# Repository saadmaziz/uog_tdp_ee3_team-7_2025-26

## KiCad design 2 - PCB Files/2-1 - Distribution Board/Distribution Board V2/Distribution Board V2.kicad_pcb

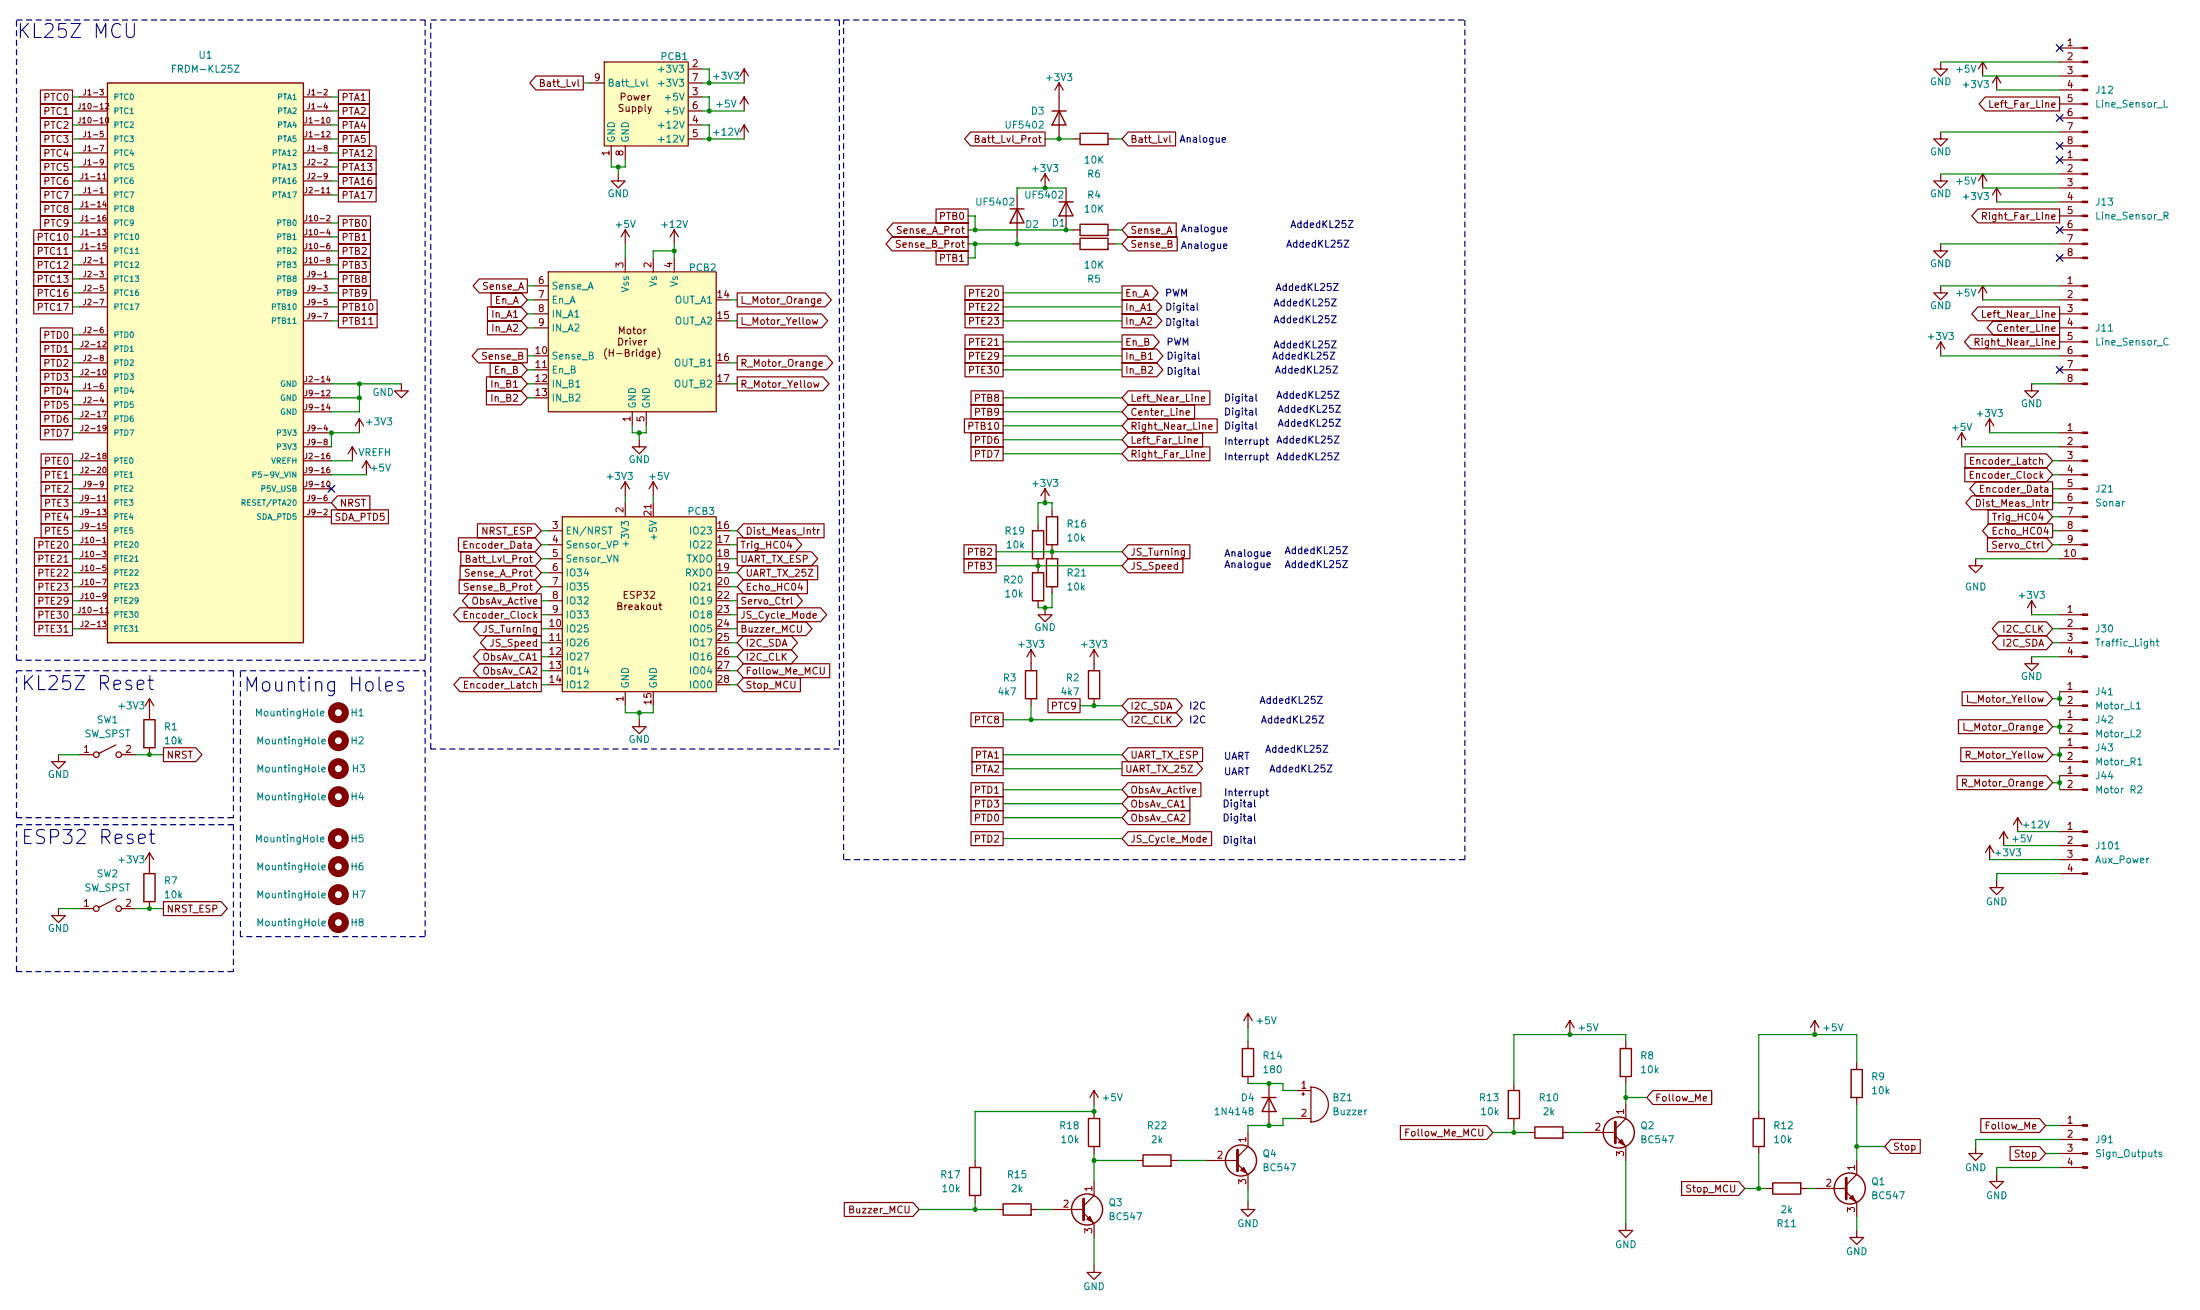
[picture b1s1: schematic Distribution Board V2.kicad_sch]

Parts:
BZ1: Buzzer; Buzzer_D14mm_H7mm_P10mm
D1, D2, D3: UF5402; D_DO-201AD_P15.24mm_Horizontal
D4: 1N4148; D_DO-35_SOD27_P7.62mm_Horizontal
H1, H2, H3, H4, H5, H6, H7, H8: MountingHole; MountingHole_3.2mm_M3
J11: Line_Sensor_C; Molex_KK-254_AE-6410-08A_1x08_P2.54mm_Vertical
J12: Line_Sensor_L; Molex_KK-254_AE-6410-08A_1x08_P2.54mm_Vertical
J13: Line_Sensor_R; Molex_KK-254_AE-6410-08A_1x08_P2.54mm_Vertical
J21: Sonar; Molex_KK-254_AE-6410-10A_1x10_P2.54mm_Vertical
J30: Traffic_Light; Molex_KK-254_AE-6410-04A_1x04_P2.54mm_Vertical
J41: Motor_L1; Molex_KK-254_AE-6410-02A_1x02_P2.54mm_Vertical
J42: Motor_L2; Molex_KK-254_AE-6410-02A_1x02_P2.54mm_Vertical
J43: Motor_R1; Molex_KK-254_AE-6410-02A_1x02_P2.54mm_Vertical
J44: Motor R2; Molex_KK-254_AE-6410-02A_1x02_P2.54mm_Vertical
J91: Sign_Outputs; Molex_KK-254_AE-6410-04A_1x04_P2.54mm_Vertical
J101: Aux_Power; Molex_KK-254_AE-6410-04A_1x04_P2.54mm_Vertical
PCB1: PSU; Power_Supply
PCB2: Motor_Driver; Motor_Controller
PCB3: ESP32; ESP32_Breakout
Q1, Q2, Q3, Q4: BC547; TO-92_Inline_Wide
R1, R7, R8, R9, R12, R13, R16, R17, R18, R19, R20, R21: 10k; R_0805_2012Metric_Pad1.20x1.40mm_HandSolder
R2, R3: 4k7; R_0805_2012Metric_Pad1.20x1.40mm_HandSolder
R4, R5, R6: 10K; R_0805_2012Metric_Pad1.20x1.40mm_HandSolder
R10, R11, R15, R22: 2k; R_0805_2012Metric_Pad1.20x1.40mm_HandSolder
R14: 180; R_0805_2012Metric_Pad1.20x1.40mm_HandSolder
SW1, SW2: SW_SPST; SW_PUSH_1P1T_6x3.5mm_H4.3_APEM_MJTP1243
U1: FRDM-KL25Z

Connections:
+3V3: D1.1 (K), D2.1 (K), D3.1 (K), J11.6, J12.4, J13.4, J21.1, J30.1, J101.3, PCB1.2 (+3V3), PCB1.7 (+3V3), PCB3.2 (+3V3), R1.1, R2.1, R3.1, R7.1, R16.2, R19.2, U1.J9-4 (P3V3), U1.J9-8 (P3V3)
+5V: J11.2, J12.3, J13.3, J21.2, J101.2, PCB1.3 (+5V), PCB1.6 (+5V), PCB2.3 (Vss), PCB3.21 (+5V), R8.1, R9.1, R12.1, R13.1, R14.1, R17.1, R18.1, U1.J9-16 (P5-9V_VIN)
+12V: J101.1, PCB1.4 (+12V), PCB1.5 (+12V), PCB2.2 (Vs), PCB2.4 (Vs)
Batt_Lvl: PCB1.9 (Batt_Lvl), R6.2
Batt_Lvl_Prot: D3.2 (A), PCB3.5 (Sensor_VN), R6.1
Buzzer_MCU: PCB3.24 (IO05), R15.1, R17.2
Center_Line: J11.4, U1.J9-3 (PTB9)
Dist_Meas_Intr: J21.6, PCB3.16 (IO23)
Echo_HC04: J21.8, PCB3.20 (IO21)
En_A: PCB2.7 (En_A), U1.J10-1 (PTE20)
En_B: PCB2.11 (En_B), U1.J10-3 (PTE21)
Encoder_Clock: J21.4, PCB3.9 (IO33)
Encoder_Data: J21.5, PCB3.4 (Sensor_VP)
Encoder_Latch: J21.3, PCB3.14 (IO12)
Follow_Me: J91.1, Q2.1 (C), R8.2
Follow_Me_MCU: PCB3.27 (IO04), R10.1, R13.2
GND: J11.1, J11.8, J12.2, J12.7, J13.2, J13.7, J21.10, J30.4, J91.2, J91.4, J101.4, PCB1.1 (GND), PCB1.8 (GND), PCB2.1 (GND), PCB2.5 (GND), PCB3.1 (GND), PCB3.15 (GND), Q1.3 (E), Q2.3 (E), Q3.3 (E), Q4.3 (E), R20.1, R21.1, SW1.1 (A), SW2.1 (A), U1.J2-14 (GND), U1.J9-12 (GND), U1.J9-14 (GND)
I2C_CLK: J30.2, PCB3.26 (IO16), R3.2, U1.J1-14 (PTC8)
I2C_SDA: J30.3, PCB3.25 (IO17), R2.2, U1.J1-16 (PTC9)
In_A1: PCB2.8 (IN_A1), U1.J10-5 (PTE22)
In_A2: PCB2.9 (IN_A2), U1.J10-7 (PTE23)
In_B1: PCB2.12 (IN_B1), U1.J10-9 (PTE29)
In_B2: PCB2.13 (IN_B2), U1.J10-11 (PTE30)
JS_Cycle_Mode: PCB3.23 (IO18), U1.J2-8 (PTD2)
JS_Speed: PCB3.11 (IO26), R19.1, R20.2, U1.J10-8 (PTB3)
JS_Turning: PCB3.10 (IO25), R16.1, R21.2, U1.J10-6 (PTB2)
L_Motor_Orange: J42.1, J42.2, PCB2.14 (OUT_A1)
L_Motor_Yellow: J41.1, J41.2, PCB2.15 (OUT_A2)
Left_Far_Line: J12.5, U1.J2-17 (PTD6)
Left_Near_Line: J11.3, U1.J9-1 (PTB8)
NRST: R1.2, SW1.2 (B), U1.J9-6 (RESET/PTA20)
NRST_ESP: PCB3.3 (EN/NRST), R7.2, SW2.2 (B)
unnamed: BZ1.1 (+), D4.1 (K), R14.2
unnamed: BZ1.2 (-), D4.2 (A), Q4.1 (C)
unnamed: Q1.2 (B), R11.2
unnamed: Q2.2 (B), R10.2
unnamed: Q3.2 (B), R15.2
unnamed: Q3.1 (C), R18.2, R22.1
unnamed: Q4.2 (B), R22.2
ObsAv_Active: PCB3.8 (IO32), U1.J2-12 (PTD1)
ObsAv_CA1: PCB3.12 (IO27), U1.J2-10 (PTD3)
ObsAv_CA2: PCB3.13 (IO14), U1.J2-6 (PTD0)
PTA1: PCB3.18 (TXDO), U1.J1-2 (PTA1)
PTA2: PCB3.19 (RXDO), U1.J1-4 (PTA2)
PTA4: U1.J1-10 (PTA4)
PTA5: U1.J1-12 (PTA5)
PTA12: U1.J1-8 (PTA12)
PTA13: U1.J2-2 (PTA13)
PTA16: U1.J2-9 (PTA16)
PTA17: U1.J2-11 (PTA17)
PTB0: D1.2 (A), PCB3.6 (IO34), R4.1, U1.J10-2 (PTB0)
PTB1: D2.2 (A), PCB3.7 (IO35), R5.1, U1.J10-4 (PTB1)
PTB10: J11.5, U1.J9-5 (PTB10)
PTB11: U1.J9-7 (PTB11)
PTC0: U1.J1-3 (PTC0)
PTC1: U1.J10-12 (PTC1)
PTC2: U1.J10-10 (PTC2)
PTC3: U1.J1-5 (PTC3)
PTC4: U1.J1-7 (PTC4)
PTC5: U1.J1-9 (PTC5)
PTC6: U1.J1-11 (PTC6)
PTC7: U1.J1-1 (PTC7)
PTC10: U1.J1-13 (PTC10)
PTC11: U1.J1-15 (PTC11)
PTC12: U1.J2-1 (PTC12)
PTC13: U1.J2-3 (PTC13)
PTC16: U1.J2-5 (PTC16)
PTC17: U1.J2-7 (PTC17)
PTD4: U1.J1-6 (PTD4)
PTD5: U1.J2-4 (PTD5)
PTD7: J13.5, U1.J2-19 (PTD7)
PTE0: U1.J2-18 (PTE0)
PTE1: U1.J2-20 (PTE1)
PTE2: U1.J9-9 (PTE2)
PTE3: U1.J9-11 (PTE3)
PTE4: U1.J9-13 (PTE4)
PTE5: U1.J9-15 (PTE5)
PTE31: U1.J2-13 (PTE31)
R_Motor_Orange: J44.1, J44.2, PCB2.16 (OUT_B1)
R_Motor_Yellow: J43.1, J43.2, PCB2.17 (OUT_B2)
SDA_PTD5: U1.J9-2 (SDA_PTD5)
Sense_A: PCB2.6 (Sense_A), R4.2
Sense_B: PCB2.10 (Sense_B), R5.2
Servo_Ctrl: J21.9, PCB3.22 (IO19)
Stop: J91.3, Q1.1 (C), R9.2
Stop_MCU: PCB3.28 (IO00), R11.1, R12.2
Trig_HC04: J21.7, PCB3.17 (IO22)
VREFH: U1.J2-16 (VREFH)

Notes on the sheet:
Analogue
UART
Mounting Holes
Interrupt
PWM
AddedKL25Z
Digital
ESP32 Reset
KL25Z Reset
KL25Z MCU
I2C

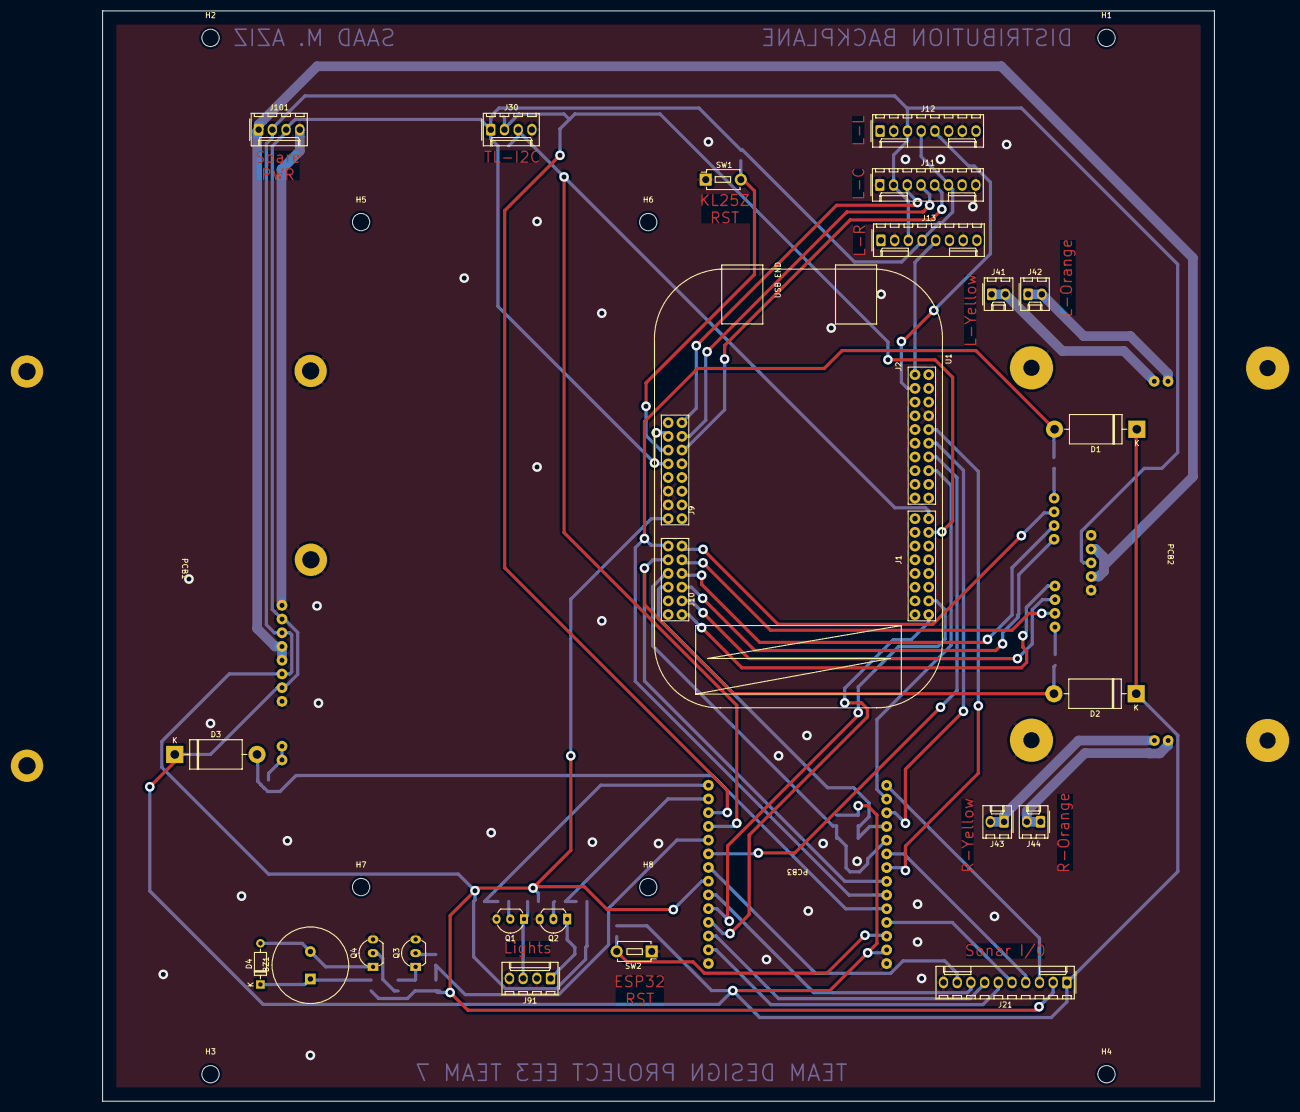
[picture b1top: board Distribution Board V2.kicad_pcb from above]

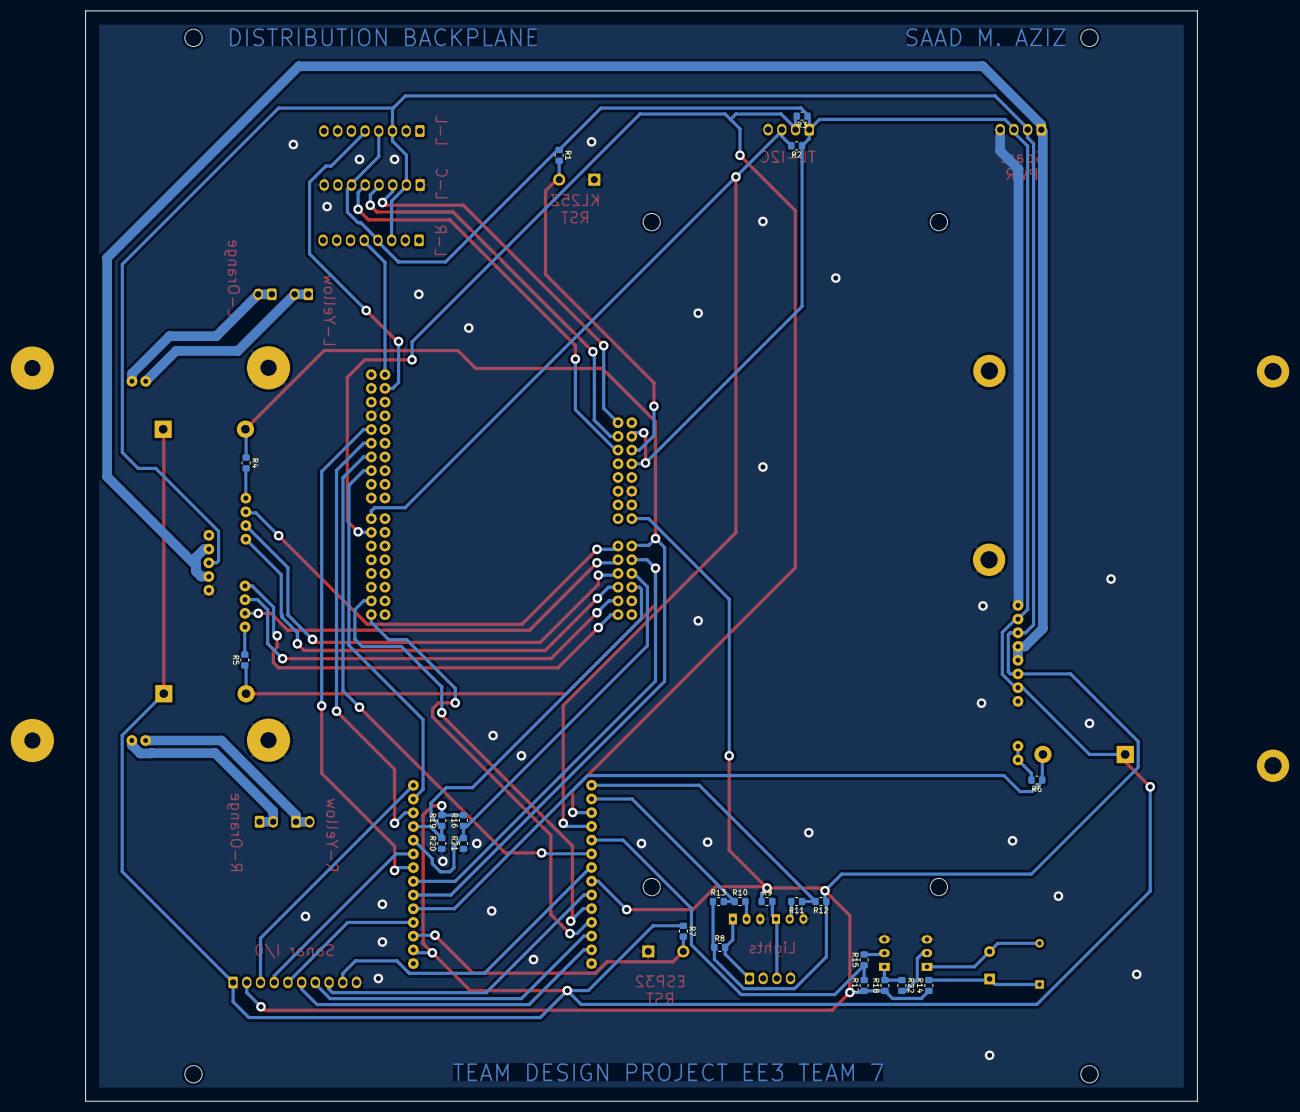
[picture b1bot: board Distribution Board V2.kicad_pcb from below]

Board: 2 copper layers, 206.0 x 202.0 mm, 56 parts (22 on the bottom side), 56 nets.

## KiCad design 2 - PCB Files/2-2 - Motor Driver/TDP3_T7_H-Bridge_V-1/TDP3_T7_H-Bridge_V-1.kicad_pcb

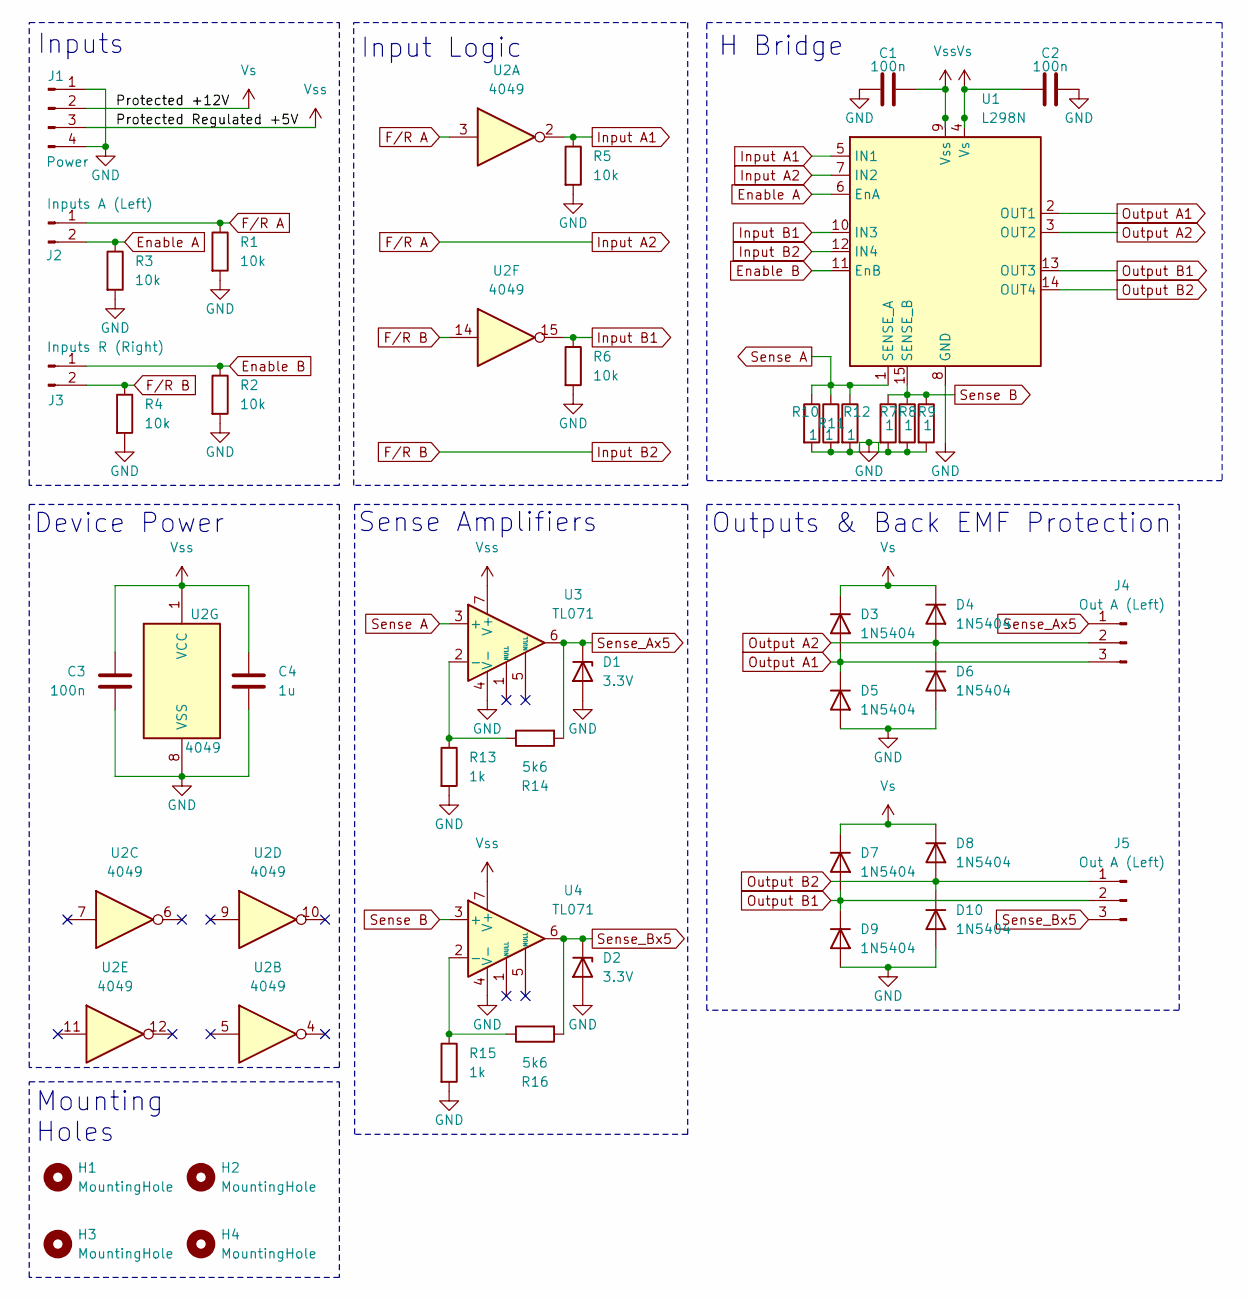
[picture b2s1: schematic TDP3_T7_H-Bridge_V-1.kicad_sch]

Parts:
C1, C2, C3: 100n; C_0805_2012Metric_Pad1.18x1.45mm_HandSolder
C4: 1u; C_0805_2012Metric_Pad1.18x1.45mm_HandSolder
D1, D2: 3.3V; D_DO-41_SOD81_P7.62mm_Horizontal
D3, D4, D5, D6, D7, D8, D9, D10: 1N5404; D_DO-201AD_P12.70mm_Horizontal
H1, H2, H3, H4: MountingHole; MountingHole_3.2mm_M3
J1: Power; Molex_KK-254_AE-6410-04A_1x04_P2.54mm_Vertical
J2: Inputs A (Left); Molex_KK-254_AE-6410-02A_1x02_P2.54mm_Vertical
J3: Inputs R (Right); Molex_KK-254_AE-6410-02A_1x02_P2.54mm_Vertical
J4, J5: Out A (Left); Molex_KK-254_AE-6410-03A_1x03_P2.54mm_Vertical
R1, R2, R3, R4, R5, R6: 10k; R_0805_2012Metric_Pad1.20x1.40mm_HandSolder
R7, R8, R9, R10, R11, R12: 1; R_Axial_DIN0207_L6.3mm_D2.5mm_P2.54mm_Vertical
R13, R15: 1k; R_0805_2012Metric_Pad1.20x1.40mm_HandSolder
R14, R16: 5k6; R_0805_2012Metric_Pad1.20x1.40mm_HandSolder
U1: L298N; L298N Heatsink
U2: 4049; DIP-16_W7.62mm
U3, U4: TL071; DIP-8_W7.62mm

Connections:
Enable A: J2.2, R3.1, U1.6 (EnA)
Enable B: J3.1, R2.1, U1.11 (EnB)
F/R A: J2.1, R1.1, U1.7 (IN2), U2.3
F/R B: J3.2, R4.1, U1.12 (IN4), U2.14
GND: C1.1, C2.2, C3.2, C4.2, D1.2 (A), D2.2 (A), D5.2 (A), D6.2 (A), D9.2 (A), D10.2 (A), J1.1, J1.4, R1.2, R2.2, R3.2, R4.2, R5.2, R6.2, R7.2, R8.2, R9.2, R10.2, R11.2, R12.2, R13.2, R15.2, U1.8 (GND), U2.8 (VSS), U3.4 (V-), U4.4 (V-)
Input A1: R5.1, U1.5 (IN1), U2.2
Input B1: R6.1, U1.10 (IN3), U2.15
unnamed: R13.1, R14.1, U3.2 (-)
unnamed: R15.1, R16.1, U4.2 (-)
Output A1: D3.2 (A), D5.1 (K), J4.3, U1.2 (OUT1)
Output A2: D4.2 (A), D6.1 (K), J4.2, U1.3 (OUT2)
Output B1: D7.2 (A), D9.1 (K), J5.2, U1.13 (OUT3)
Output B2: D8.2 (A), D10.1 (K), J5.1, U1.14 (OUT4)
Sense A: R10.1, R11.1, R12.1, U1.1 (SENSE_A), U3.3 (+)
Sense B: R7.1, R8.1, R9.1, U1.15 (SENSE_B), U4.3 (+)
Sense_Ax5: D1.1 (K), J4.1, R14.2, U3.6
Sense_Bx5: D2.1 (K), J5.3, R16.2, U4.6
Vs: C2.1, D3.1 (K), D4.1 (K), D7.1 (K), D8.1 (K), J1.2, U1.4 (Vs)
Vss: C1.2, C3.1, C4.1, J1.3, U1.9 (Vss), U2.1 (VCC), U3.7 (V+), U4.7 (V+)

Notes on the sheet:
Device Power
Input Logic
Mounting Holes
Inputs
Outputs & Back EMF Protection
H Bridge
Sense Amplifiers

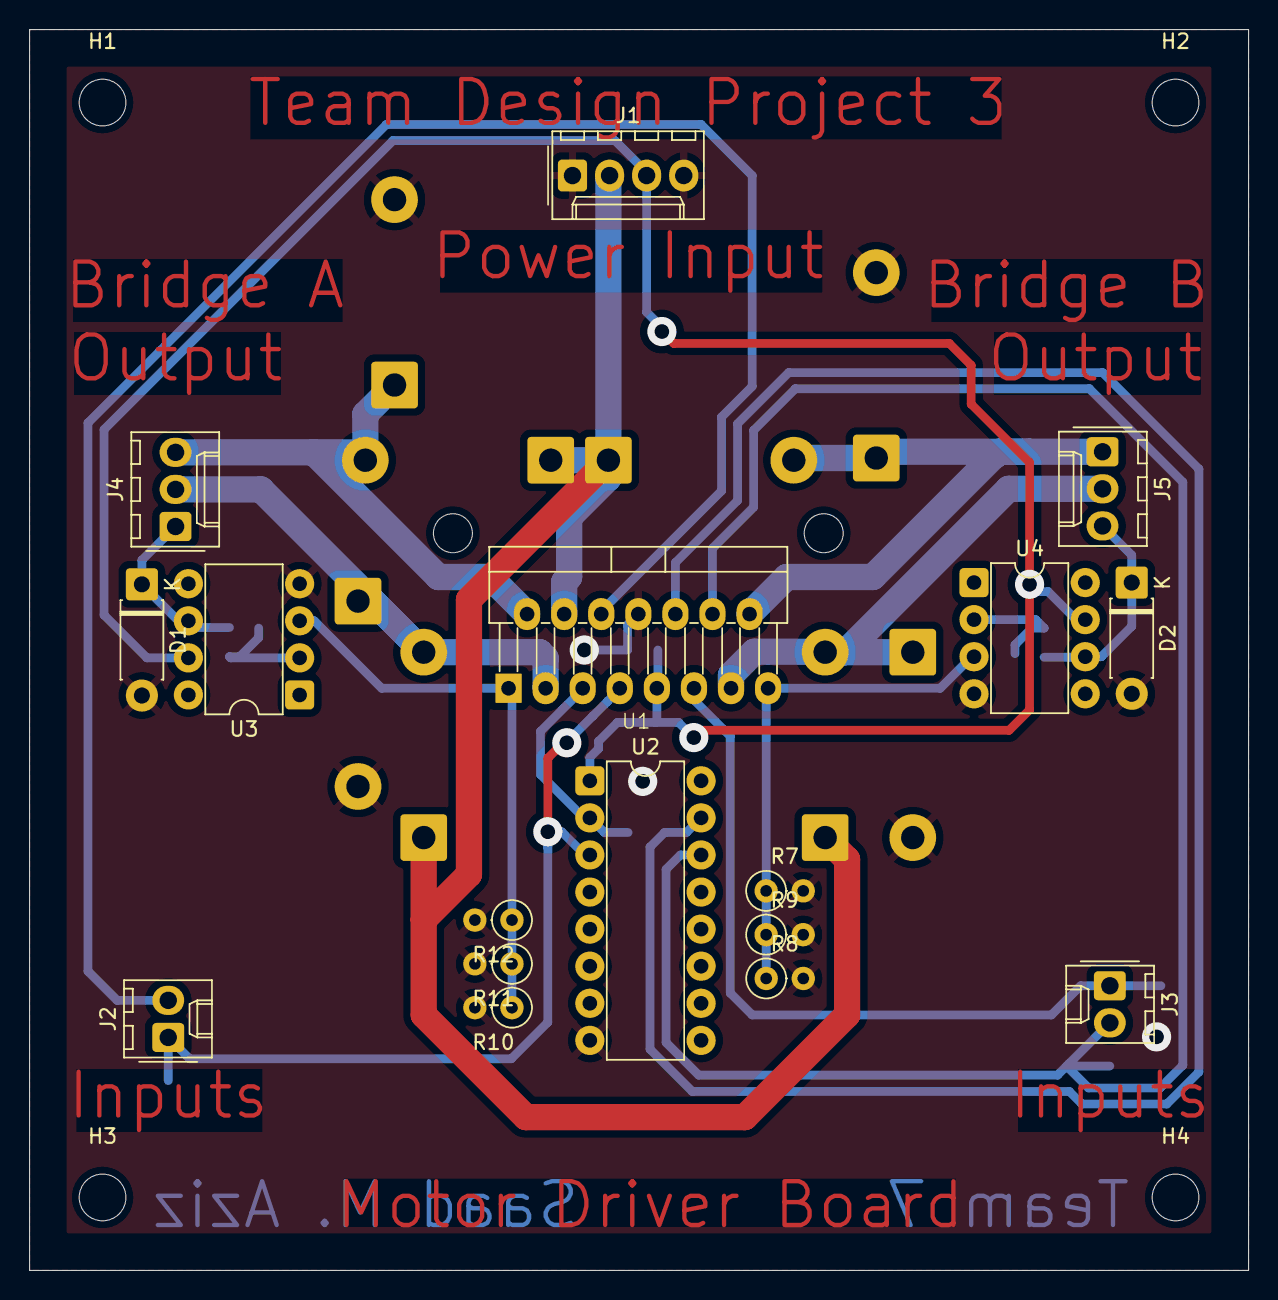
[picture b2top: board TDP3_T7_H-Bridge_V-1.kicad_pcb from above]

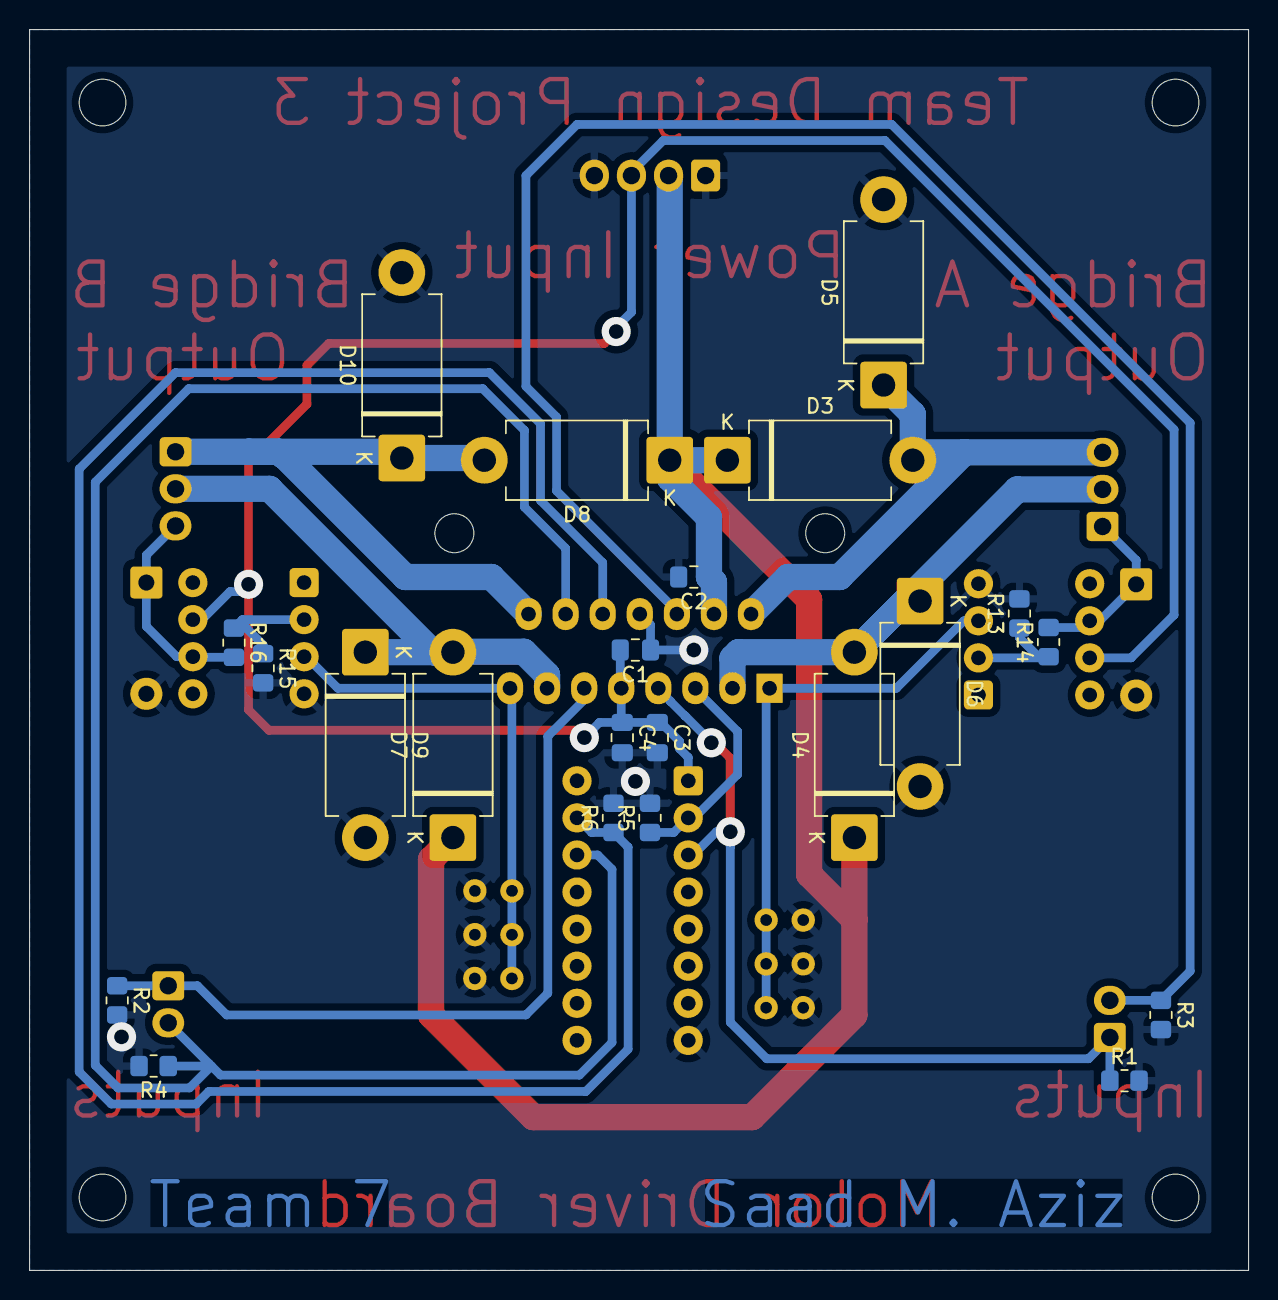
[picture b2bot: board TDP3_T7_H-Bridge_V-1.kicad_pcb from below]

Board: 2 copper layers, 83.5 x 85.0 mm, 43 parts (22 on the bottom side), 19 nets.

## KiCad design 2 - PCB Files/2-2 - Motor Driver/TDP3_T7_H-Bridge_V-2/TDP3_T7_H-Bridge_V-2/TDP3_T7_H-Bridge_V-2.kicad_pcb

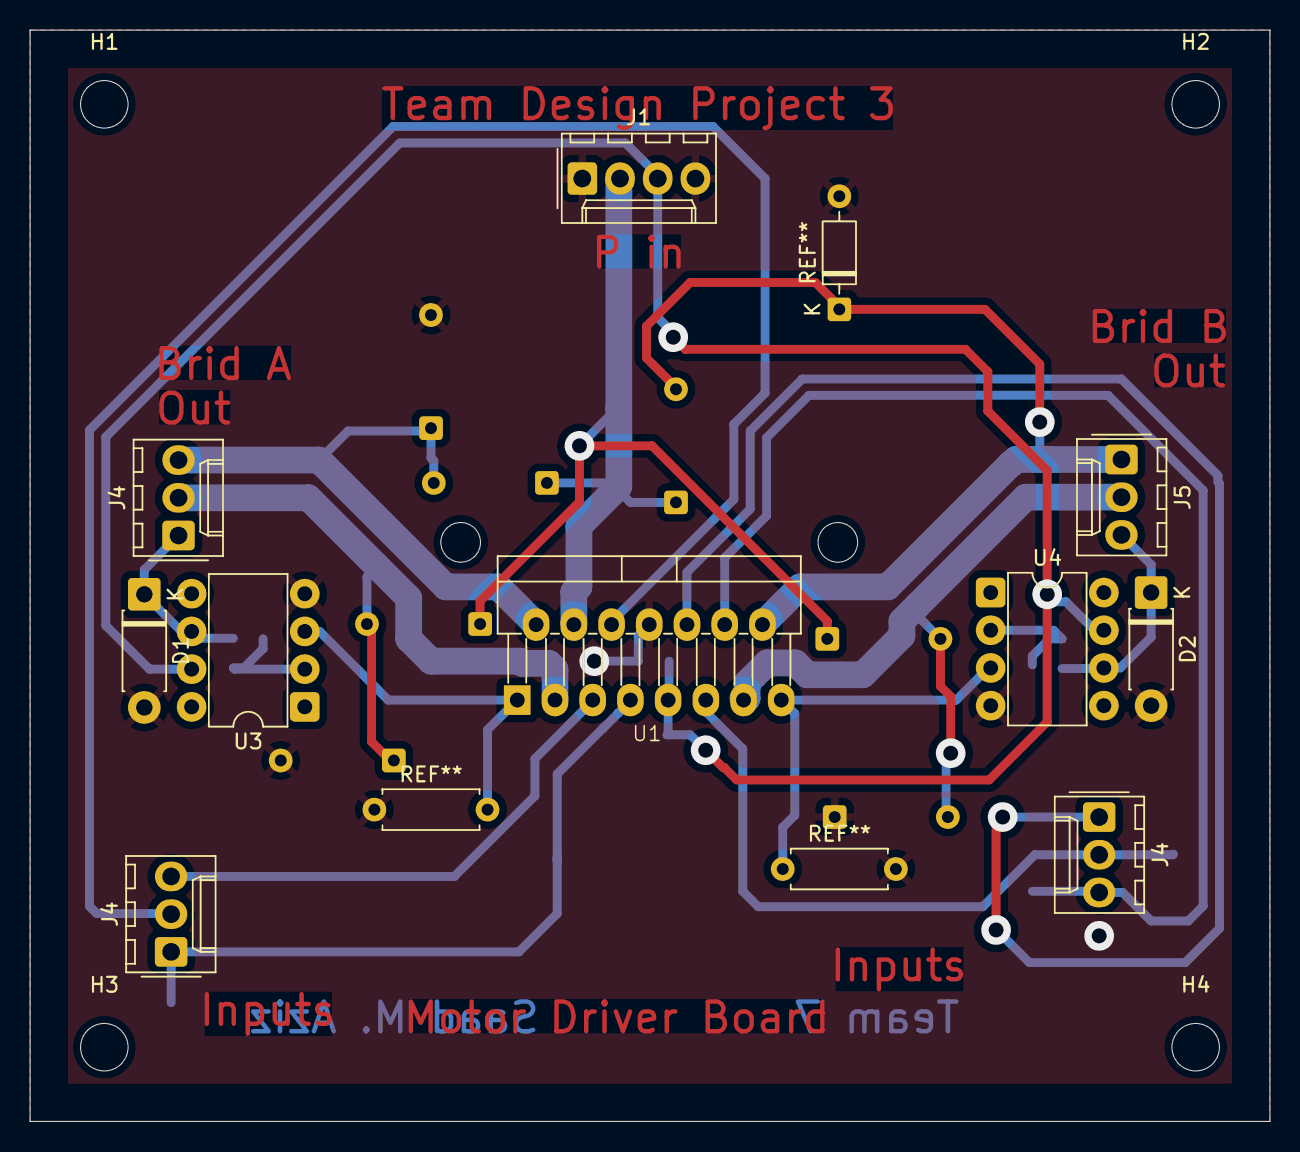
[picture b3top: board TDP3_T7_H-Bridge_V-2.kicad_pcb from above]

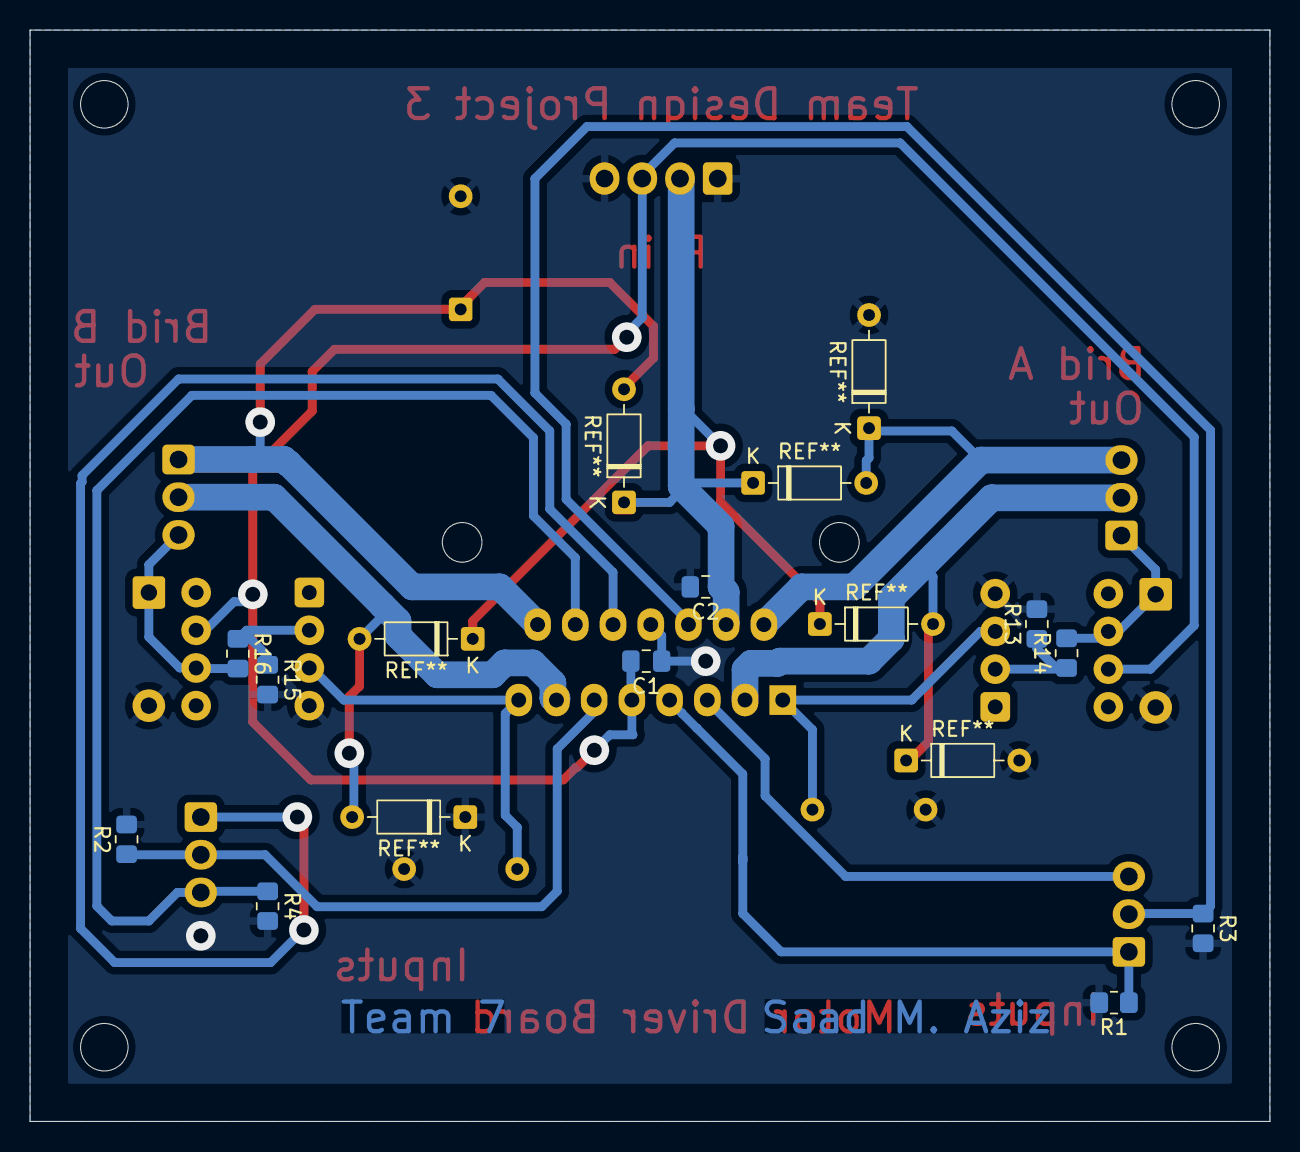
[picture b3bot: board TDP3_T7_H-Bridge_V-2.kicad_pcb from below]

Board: 2 copper layers, 83.5 x 73.5 mm, 24 parts (10 on the bottom side), 19 nets.

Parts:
C1, C2: 100n; C_0805_2012Metric_Pad1.18x1.45mm_HandSolder
D1, D2: 3.3V; D_DO-41_SOD81_P7.62mm_Horizontal
H1, H2, H3, H4: MountingHole; MountingHole_3.2mm_M3
J1: Power; Molex_KK-254_AE-6410-04A_1x04_P2.54mm_Vertical
J4, J4#2, J4#3, J5: Out A (Left); Molex_KK-254_AE-6410-03A_1x03_P2.54mm_Vertical
R1, R2, R3, R4: 10k; R_0805_2012Metric_Pad1.20x1.40mm_HandSolder
R13, R15: 1k; R_0805_2012Metric_Pad1.20x1.40mm_HandSolder
R14, R16: 5k6; R_0805_2012Metric_Pad1.20x1.40mm_HandSolder
U1: L298N; L298N Heatsink
U3, U4: TL071; DIP-8_W7.62mm

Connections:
Enable A: J4#3.2, R3.1, U1.6 (EnA)
Enable B: J4#2.2, R2.1, U1.11 (EnB)
F/R A: J4#3.1, R1.1, U1.7 (IN2)
F/R B: J4#2.3, R4.1, U1.12 (IN4)
GND: C1.1, C2.2, D1.2 (A), D2.2 (A), J1.1, J1.4, R1.2, R2.2, R3.2, R4.2, R13.2, R15.2, U1.8 (GND), U3.4 (V-), U4.4 (V-)
Input A1: J4#3.3, U1.5 (IN1)
Input B1: J4#2.1, U1.10 (IN3)
unnamed: R13.1, R14.1, U3.2 (-)
unnamed: R15.1, R16.1, U4.2 (-)
Output A1: J4.3, U1.2 (OUT1)
Output A2: J4.2, U1.3 (OUT2)
Output B1: J5.2, U1.13 (OUT3)
Output B2: J5.1, U1.14 (OUT4)
Sense A: U1.1 (SENSE_A), U3.3 (+)
Sense B: U1.15 (SENSE_B), U4.3 (+)
Sense_Ax5: D1.1 (K), J4.1, R14.2, U3.6
Sense_Bx5: D2.1 (K), J5.3, R16.2, U4.6
Vs: C2.1, J1.2, U1.4 (Vs)
Vss: C1.2, J1.3, U1.9 (Vss), U3.7 (V+), U4.7 (V+)

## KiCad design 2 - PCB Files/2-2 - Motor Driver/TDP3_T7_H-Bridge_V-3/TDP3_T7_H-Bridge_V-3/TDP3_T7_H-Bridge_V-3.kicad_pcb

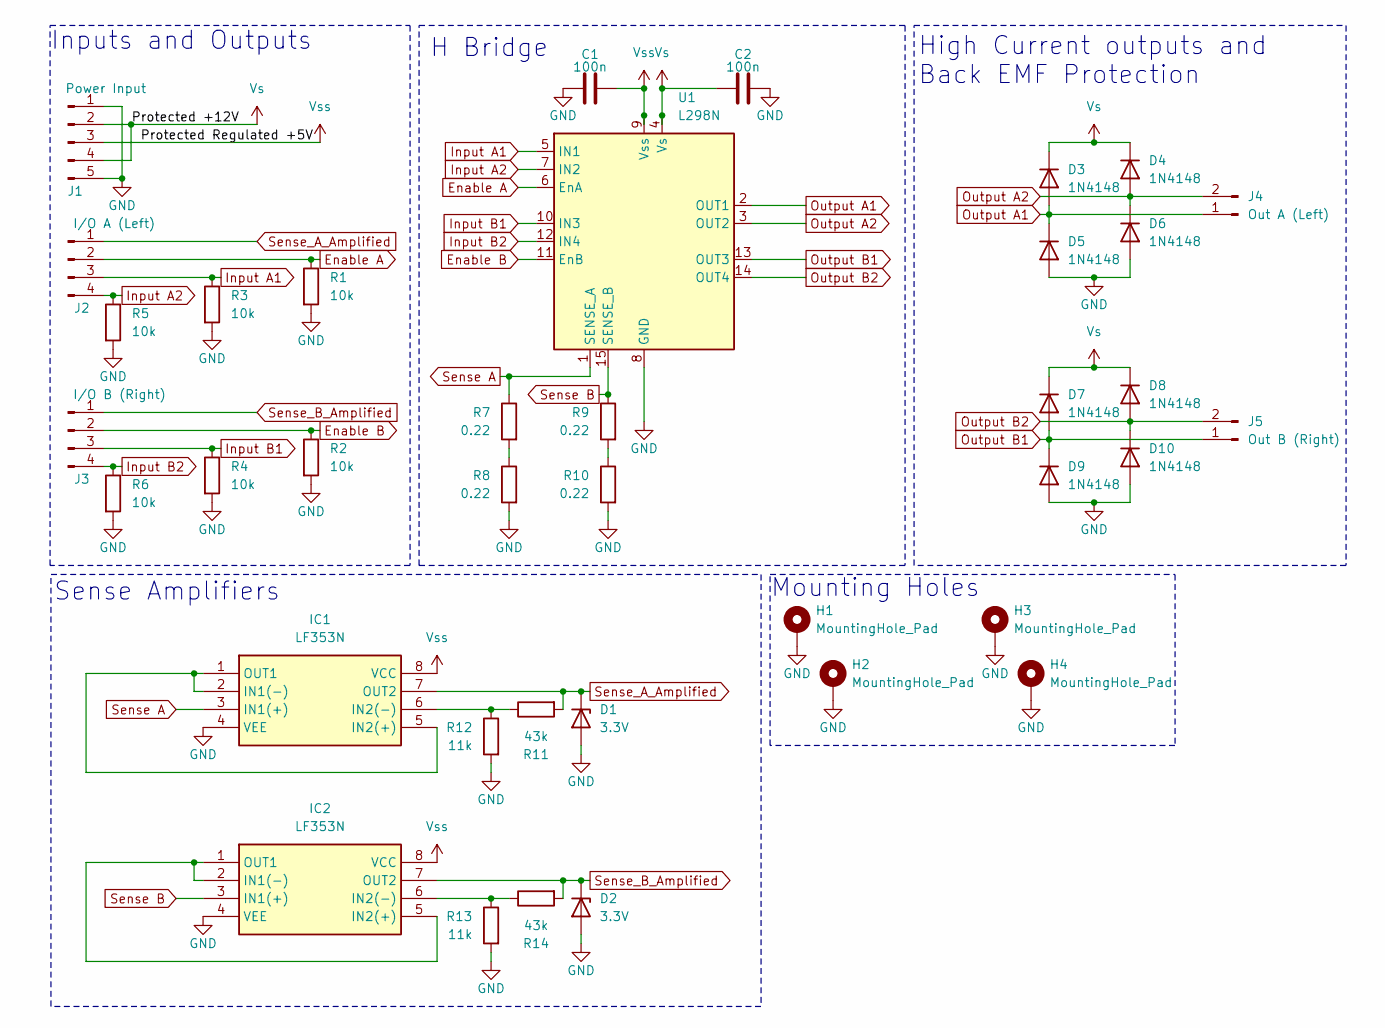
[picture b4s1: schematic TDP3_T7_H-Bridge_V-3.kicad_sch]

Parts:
C1, C2: 100n; C_0805_2012Metric_Pad1.18x1.45mm_HandSolder
D1, D2: 3.3V; D_DO-41_SOD81_P7.62mm_Horizontal
D3, D4, D5, D6, D7, D8, D9, D10: 1N4148; D_DO-35_SOD27_P7.62mm_Horizontal
H1, H2, H3, H4: MountingHole_Pad; MountingHole_4.3mm_M4_DIN965_Pad_TopBottom
IC1, IC2: LF353N; DIP-8_W7.62mm_LongPads; Manufacturer_Part_Number LF353N; Mouser Part Number 926-LF353N
J1: Power Input; PinHeader_1x05_P2.54mm_Vertical
J2: I/O A (Left); PinHeader_1x04_P2.54mm_Vertical
J3: I/O B (Right); PinHeader_1x04_P2.54mm_Vertical
J4: Out A (Left); PinHeader_1x02_P2.54mm_Vertical
J5: Out B (Right); PinHeader_1x02_P2.54mm_Vertical
R1, R2, R3, R4, R5, R6: 10k; R_0805_2012Metric_Pad1.20x1.40mm_HandSolder
R7, R8, R9, R10: 0.22; R_1206_3216Metric_Pad1.30x1.75mm_HandSolder
R11, R14: 43k; R_0805_2012Metric_Pad1.20x1.40mm_HandSolder
R12, R13: 11k; R_0805_2012Metric_Pad1.20x1.40mm_HandSolder
U1: L298N; L298N Heatsink

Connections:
Enable A: J2.2, R1.1, U1.6 (EnA)
Enable B: J3.2, R2.1, U1.11 (EnB)
GND: C1.1, C2.2, D1.2 (A), D2.2 (A), D5.2 (A), D6.2 (A), D9.2 (A), D10.2 (A), H1.1, H2.1, H3.1, H4.1, IC1.4 (VEE), IC2.4 (VEE), J1.1, J1.5, R1.2, R2.2, R3.2, R4.2, R5.2, R6.2, R8.2, R10.2, R12.2, R13.2, U1.8 (GND)
Input A1: J2.3, R3.1, U1.5 (IN1)
Input A2: J2.4, R5.1, U1.7 (IN2)
Input B1: J3.3, R4.1, U1.10 (IN3)
Input B2: J3.4, R6.1, U1.12 (IN4)
unnamed: IC1.1 (OUT1), IC1.2 (IN1(-)), IC1.5 (IN2(+))
unnamed: IC1.6 (IN2(-)), R11.1, R12.1
unnamed: IC2.1 (OUT1), IC2.2 (IN1(-)), IC2.5 (IN2(+))
unnamed: IC2.6 (IN2(-)), R13.1, R14.1
unnamed: R7.2, R8.1
unnamed: R9.2, R10.1
Output A1: D3.2 (A), D5.1 (K), J4.1, U1.2 (OUT1)
Output A2: D4.2 (A), D6.1 (K), J4.2, U1.3 (OUT2)
Output B1: D7.2 (A), D9.1 (K), J5.1, U1.13 (OUT3)
Output B2: D8.2 (A), D10.1 (K), J5.2, U1.14 (OUT4)
Sense A: IC1.3 (IN1(+)), R7.1, U1.1 (SENSE_A)
Sense B: IC2.3 (IN1(+)), R9.1, U1.15 (SENSE_B)
Sense_A_Amplified: D1.1 (K), IC1.7 (OUT2), J2.1, R11.2
Sense_B_Amplified: D2.1 (K), IC2.7 (OUT2), J3.1, R14.2
Vs: C2.1, D3.1 (K), D4.1 (K), D7.1 (K), D8.1 (K), J1.2, J1.4, U1.4 (Vs)
Vss: C1.2, IC1.8 (VCC), IC2.8 (VCC), J1.3, U1.9 (Vss)

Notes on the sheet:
High Current outputs and Back EMF Protection
Mounting Holes
Inputs and Outputs
H Bridge
Sense Amplifiers
